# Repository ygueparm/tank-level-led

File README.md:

🔍 **Menu de navigation rapide**
- [🔧 How It Works](#-How-It-Works)
- [📊 Calibration & Real-World Parameters](#-calibration--real-world-parameters)
- [🌟 Key Features](#-key-features)
- [🔧 Wiring Hint](#-wiring-hint)
- [🙏 Acknowledgments](#acknowledgments)

---

## 🔧 How It Works
1bar = 10 meter (approximatly)

This system monitors and visualizes the fill level of an underground fuel/oil tank using:

    A 0–1 bar pressure sensor (measuring static head pressure),
    An Arduino Nano for signal processing and control,
    A 8-LED bar for intuitive visual feedback,
    A solid-state relay (SSR) to automate a pump based on level thresholds.

## 📊 Calibration & Real-World Parameters

in my home my tank is outdoor, and at 2 meter, i use it for the garden, and full it with a pump from underground or rain water, so i bought a 4-20 pressure sensors t osee if i need to full it or not

All calculations are based on empirical measurements (not just theoretical formulas), making the system robust to sensor drift or installation-specific conditions:
Parameter
	
Value
Empty tank  0.00 bar (4.28 mA)

Full tank 0.21 bar (7.46 mA)

Pump shut-off (dynamic) 0.43 bar (prevents overfill during pump operation)

Pump start threshold ≤15% level

10-sample moving average on analog readings
## 🌟 Key Features

    ✅ Startup LED test — visual confirmation of all LEDs and level simulation  
    📈 Progressive LED bar — linear mapping of pressure → fill level (0 to 8 LEDs = 0% to 100%)  
    ⚠️ Critical-level alert — first LED blinks when level ≤10% (low fuel warning)  
    🔄 Hysteresis-based pump control — avoids rapid ON/OFF cycling with a ssr you can command a pump on D11:
        Pump starts when level ≤15%  
        Pump stops when dynamic pressure ≥ 0.43 bar (measured during pumping)
    📋 Live serial dashboard — ASCII bar graph + status in real time:

```
Affichage LED: 0.00 - 0.21 bar (0.21 = toutes LEDs)
Courant: 4.28mA (0 bar) à 20.0mA (1 bar)
Pompe: Démarre à 0.15 bar / Arrête à 0.45 bar
========================================
Pression | % Remplissage | Barre LEDs | Pompe
---------|---------------|------------|------
0.000 bar | 0.0% | ░░░░░░░░ | VIDE | OFF | Courant: 0.00mA | LED%: 0.0%
Initialisation terminée - Pression: 0.000 bar
>>> État initial: POMPE ON (niveau bas) <<<
0.000 bar | 0.0%   | ░░░░░░░░ | VIDE | ON | Courant: 0.00mA | LED%: 0.0%
0.210 bar | 100.0% | ███████░ | Pleine | OFF | Courant: 7.21mA | LED%: 100.0%
```

## 📐 Wiring Hint

    Sensor → analogPin (via shunt resistor for 4–20 mA loop)  
    LEDs → digital pins (simple HIGH/LOW, no PWM needed)  
    SSR control → pinSSR → triggers external pump contactor

    🔧 Note: The linear conversion convertirPressionReelle() uses real current-to-pressure calibration points — easily adaptable to other sensors.

# Acknowledgments

This project wouldn’t be where it is today without the generous support of the open-source hardware community—and especially **[PCBWay](https://www.pcbway.com/)**.

 I was able to fabricate a revised version (**v1.1**) of the tank-level LED controller board. The original design contained a subtle but critical pin assignment error 

Having access to physical prototypes at no cost allowed me to:
- ✅ Identify and confirm the hardware bug,
- ✅ Iterate on the layout with confidence,
- ✅ Validate signal integrity and power distribution,
- ✅ And ultimately deliver a more reliable, functional design.

PCBWay’s commitment to empowering independent developers, students, and hobbyists like me truly accelerates innovation at the grassroots level. Their fast turnaround, consistent quality, and maker-friendly approach make them a standout partner in the electronics ecosystem.

A sincere thank you to the PCBWay team—you’ve helped turn a flawed prototype into a working solution! 🙏 and i am very proud to be selected by your team

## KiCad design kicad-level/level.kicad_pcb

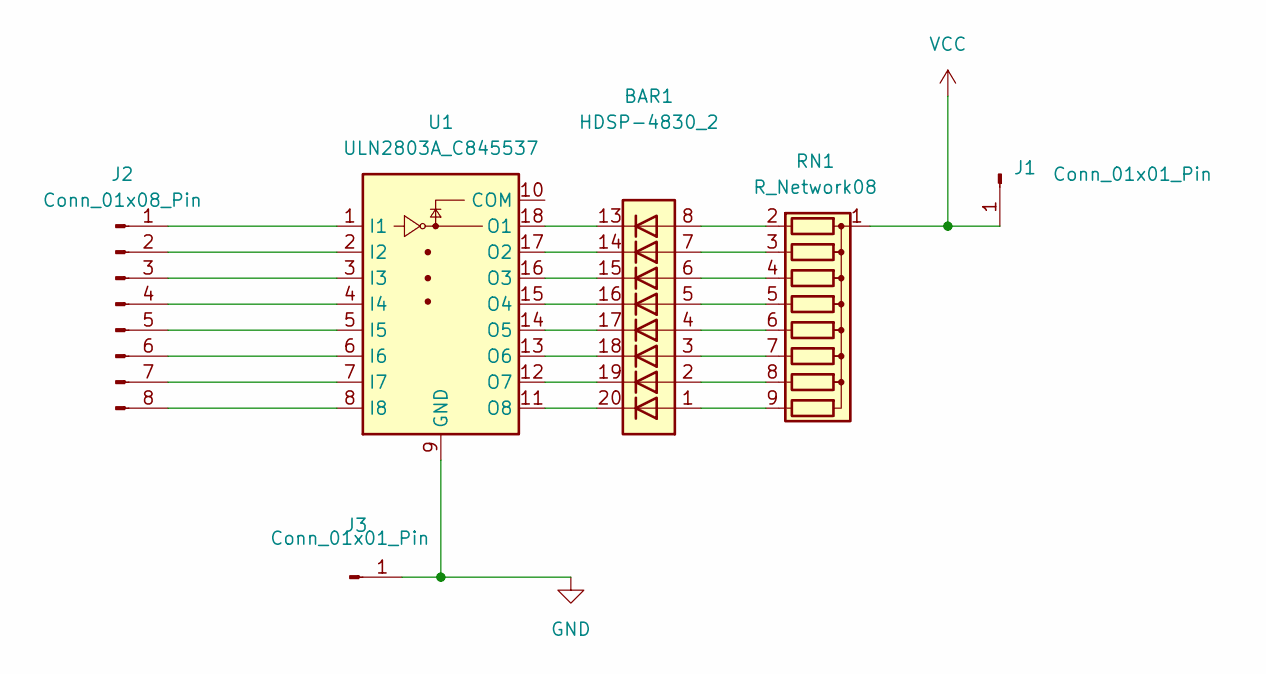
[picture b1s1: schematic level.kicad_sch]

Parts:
BAR1: HDSP-4830_2; HDSP-4830
J1, J3: Conn_01x01_Pin; PinHeader_1x01_P2.54mm_Vertical
J2: Conn_01x08_Pin; PinHeader_1x08_P2.54mm_Vertical
RN1: R_Network08; R_Array_SIP9
U1: ULN2803A_C845537; SOP-18_7x12.5mm_P1.27mm

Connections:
GND: J3.1, U1.9 (GND)
unnamed: J2.1, U1.1 (I1)
unnamed: J2.2, U1.2 (I2)
unnamed: J2.3, U1.3 (I3)
unnamed: J2.4, U1.4 (I4)
unnamed: J2.5, U1.5 (I5)
unnamed: J2.6, U1.6 (I6)
unnamed: J2.7, U1.7 (I7)
unnamed: J2.8, U1.8 (I8)
unnamed: BAR1.8 (A), RN1.2 (R1)
unnamed: BAR1.7 (A), RN1.3 (R2)
unnamed: BAR1.6 (A), RN1.4 (R3)
unnamed: BAR1.5 (A), RN1.5 (R4)
unnamed: BAR1.4 (A), RN1.6 (R5)
unnamed: BAR1.3 (A), RN1.7 (R6)
unnamed: BAR1.2 (A), RN1.8 (R7)
unnamed: BAR1.1 (A), RN1.9 (R8)
unnamed: BAR1.13 (K), U1.18 (O1)
unnamed: BAR1.14 (K), U1.17 (O2)
unnamed: BAR1.15 (K), U1.16 (O3)
unnamed: BAR1.16 (K), U1.15 (O4)
unnamed: BAR1.17 (K), U1.14 (O5)
unnamed: BAR1.18 (K), U1.13 (O6)
unnamed: BAR1.19 (K), U1.12 (O7)
unnamed: BAR1.20 (K), U1.11 (O8)
VCC: J1.1, RN1.1 (common)

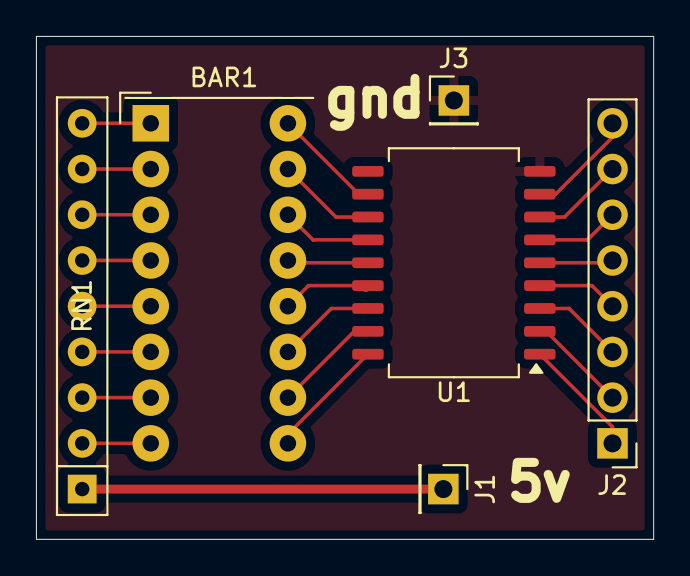
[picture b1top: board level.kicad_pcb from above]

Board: 2 copper layers, 34.3 x 27.9 mm, 6 parts (0 on the bottom side), 26 nets.

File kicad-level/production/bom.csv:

Designator,Footprint,Quantity,Value,LCSC Part #
BAR1,HDSP-4830,1,HDSP-4830_2,
"J1, J3",PinHeader_1x01_P2.54mm_Vertical,2,Conn_01x01_Pin,
J2,PinHeader_1x08_P2.54mm_Vertical,1,Conn_01x08_Pin,
RN1,R_Array_SIP9,1,R_Network08,
U1,SOP-18_7x12.5mm_P1.27mm,1,ULN2803A_C845537,

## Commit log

2025-12-12 ajout du .ino pour gerer l'afficheur et la pompe
2025-12-12 ajout du readme en anglais
2025-12-12 ajout des fichier kicad pour avoir le module led proprement commandé
2025-12-12 capture ecran
2025-12-12 capteur d'ecran
2025-12-12 Create LICENSE
2025-12-14 correction demarrage pompe niveua intermeiaure
2025-12-15 plage de pression complete, et affichage unniquement sur 0 0.21
2025-12-15 readme mis a jour
2025-12-19 erreur pcb, com a la masse
2025-12-19 mise a jour fichier production
2026-01-04 Revert "erreur pcb, com a la masse"
    This reverts commit de789b6cb290ad22ceee4c73f03ad83cfbf3b982.
2026-01-04 correction image nano mini
2026-01-04 ajout schema de montage
2026-01-04 ajout schema de montage dans le readme
2026-01-07 misa a jour pcb plus petit
2026-01-08 capture d'ecran 3D mise a jour
2026-01-08 capture ecran pcb
2026-01-08 captur eecran pcb dans readme
2026-01-11 ajout remerciement pcbway
2026-01-11 correction lien sponsor
2026-01-11 table matière readme
2026-01-17 Add files via upload
    pcb receive !
2026-01-17 Update README.md
    add photo of pcb
2026-01-23 add jpg
